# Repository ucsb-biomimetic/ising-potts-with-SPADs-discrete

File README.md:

# ising-potts-with-SPADs-discrete
CMOS compatible Ising and Potts Annealing Using Single-photon Avalanche Diodes: Design files

The proof-of-concept for SPAD Ising and Potts CTMC (continuous-time markov chain) relies on the key files provided here.  There are two sets of files for 16-circuit and 144-circuit implementations of variable rate SPADs; the 144-circuit version was created second, to enable demonstrations of combinatorial problem solving.

For each implementation, there are three groups of files: one for PCB design, one for FPGA logic, and one for data and code. The code runs tests on the physical system specified by the PCB and FPGA design, and saves data results.

For the 16-circuit version, both the code and the FPGA configuration for the system lies entirely on the Zedboard; a Vivado 2020.1 project is provided, which was used to create the Zedboard FPGA configuration. The processor side of the Zedboard was configured to run linux and the PYNQ environment, so data collection and control of the proof-of-concept aparatus was done through a jupyter-notebook running locally on the zedboard (and accessed from a PC over ethernet).

Since the provided jupyter notebook runs in concert with the Zedboard FPGA and the hardware we connect to the FPGA, it cannot be run in its entirety without fully replicating the hardware as well.  However, many intermediate data are saved alongside the notebook, so one may see the interaction between code and results.  

For the 144-circuit version, the FPGA logic was redesigned to expose a SPI interface that could be accessed over a USB connection. Thus the Python code ran directly on a PC.  In addition, the FPGA board (A Digilent Genesys 2) was configured using Vivado 2020.1 in non-project mode, so rather than a Vivado project, regular verilog files and a Vivado TCL script provided.

While many of the scripts still require a connection to the hardware to run correctly, some scripts that only perform data plotting can be run without the hardware.

All experimental data in the paper is drawn from one of the two experimental systems specified here.

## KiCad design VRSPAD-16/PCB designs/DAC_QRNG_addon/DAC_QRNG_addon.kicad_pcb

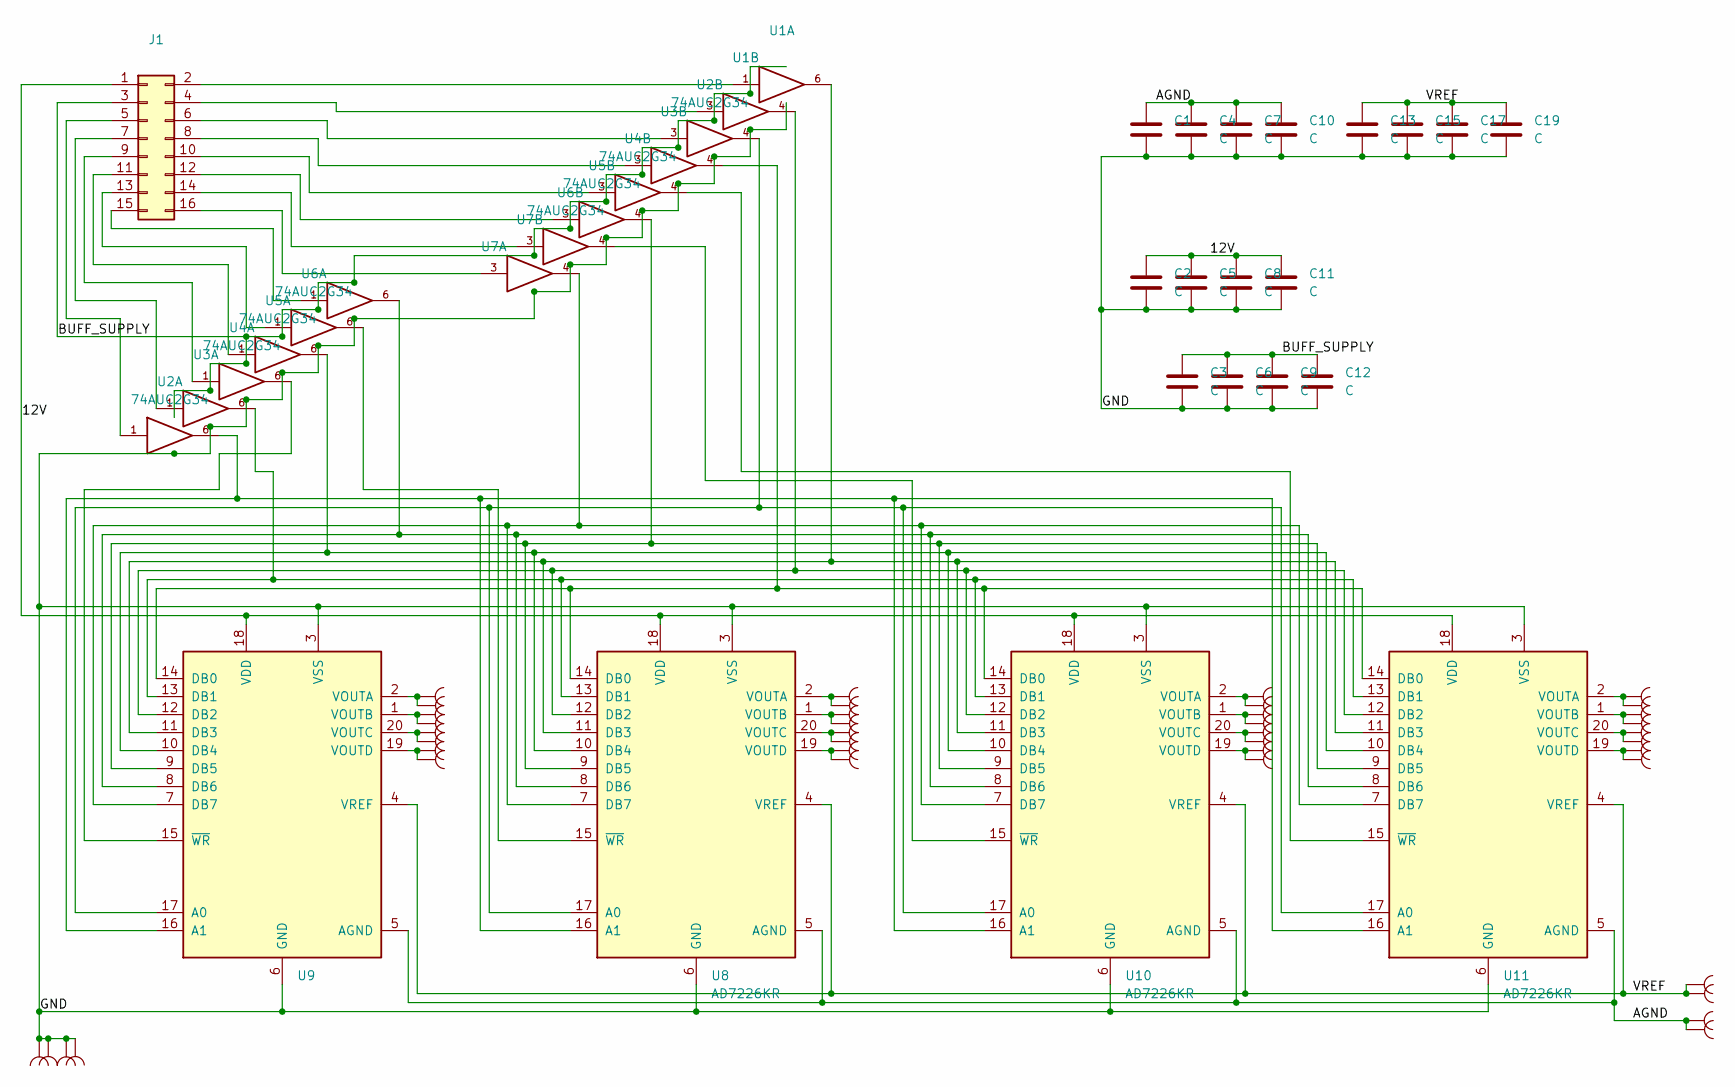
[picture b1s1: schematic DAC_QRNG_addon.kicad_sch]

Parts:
C1: (no value)
C2, C3, C4, C5, C6, C7, C8, C9, C10, C11, C12, C13, C15, C17, C19: C; C_0603_1608Metric_Pad1.08x0.95mm_HandSolder
J1: (no value)
U1, U3, U7, U9, U28, U29: (no value)
U2, U4, U5, U6: 74AUC2G34; SOT-363_SC-70-6
U8, U10, U11: AD7226KR; SOIC-20W_7.5x12.8mm_P1.27mm
U12, U13, U14, U15, U16, U17, U18, U19, U20, U21, U22, U23, U24, U25, U26, U27, U30, U31: Castle

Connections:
/12V: C2.1, C5.1, C8.1, C11.1, J1.1, U8.18 (VDD), U9.18 (VDD), U10.18 (VDD), U11.18 (VDD)
/AGND: C1.1, C4.1, C7.1, C10.1, U8.5 (AGND), U9.5 (AGND), U10.5 (AGND), U11.5 (AGND), U29.1, U29.2
/VREF: C13.1, C15.1, C17.1, C19.1, U8.4 (VREF), U9.4 (VREF), U10.4 (VREF), U11.4 (VREF), U28.1, U28.2
GND: C1.2, C2.2, C3.2, C4.2, C5.2, C6.2, C7.2, C8.2, C9.2, C10.2, C11.2, C12.2, C13.2, C15.2, C17.2, C19.2, U1.2 (GND), U2.2 (GND), U3.2 (GND), U4.2 (GND), U5.2 (GND), U6.2 (GND), U7.2 (GND), U8.3 (VSS), U8.6 (GND), U9.3 (VSS), U9.6 (GND), U10.3 (VSS), U10.6 (GND), U11.3 (VSS), U11.6 (GND), U30.1, U30.2, U31.1, U31.2
unnamed: J1.5, U2.1
unnamed: J1.6, U2.3
unnamed: J1.9, U4.1
unnamed: J1.10, U4.3
unnamed: J1.13, U6.1
unnamed: J1.14, U6.3
unnamed: J1.2, U1.1
unnamed: J1.4, U1.3
unnamed: J1.7, U3.1
unnamed: J1.8, U3.3
unnamed: J1.11, U5.1
unnamed: J1.12, U5.3
unnamed: U6.6, U8.15 (~WR)
unnamed: J1.15, U7.1
unnamed: J1.16, U7.3
unnamed: U4.6, U9.15 (~WR)
unnamed: U10.1 (VOUTB), U21.1, U21.2
unnamed: U10.2 (VOUTA), U20.1, U20.2
unnamed: U7.4, U8.7 (DB7), U9.7 (DB7), U10.7 (DB7), U11.7 (DB7)
unnamed: U7.6, U8.8 (DB6), U9.8 (DB6), U10.8 (DB6), U11.8 (DB6)
unnamed: U5.4, U8.9 (DB5), U9.9 (DB5), U10.9 (DB5), U11.9 (DB5)
unnamed: U5.6, U8.10 (DB4), U9.10 (DB4), U10.10 (DB4), U11.10 (DB4)
unnamed: U1.6, U8.11 (DB3), U9.11 (DB3), U10.11 (DB3), U11.11 (DB3)
unnamed: U1.4, U8.12 (DB2), U9.12 (DB2), U10.12 (DB2), U11.12 (DB2)
unnamed: U3.6, U8.13 (DB1), U9.13 (DB1), U10.13 (DB1), U11.13 (DB1)
unnamed: U3.4, U8.14 (DB0), U9.14 (DB0), U10.14 (DB0), U11.14 (DB0)
unnamed: U6.4, U10.15 (~WR)
unnamed: U2.6, U8.16 (A1), U9.16 (A1), U10.16 (A1), U11.16 (A1)
unnamed: U2.4, U8.17 (A0), U9.17 (A0), U10.17 (A0), U11.17 (A0)
unnamed: U10.19 (VOUTD), U23.1, U23.2
unnamed: U10.20 (VOUTC), U22.1, U22.2
unnamed: U11.1 (VOUTB), U25.1, U25.2
unnamed: U11.2 (VOUTA), U24.1, U24.2
unnamed: U4.4, U11.15 (~WR)
unnamed: U11.19 (VOUTD), U27.1, U27.2
unnamed: U11.20 (VOUTC), U26.1, U26.2
unnamed: U9.2 (VOUTA), U12.1, U12.2
unnamed: U9.1 (VOUTB), U13.1, U13.2
unnamed: U9.20 (VOUTC), U14.1, U14.2
unnamed: U9.19 (VOUTD), U15.1, U15.2
unnamed: U8.2 (VOUTA), U16.1, U16.2
unnamed: U8.1 (VOUTB), U17.1, U17.2
unnamed: U8.20 (VOUTC), U18.1, U18.2
unnamed: U8.19 (VOUTD), U19.1, U19.2
VCC: C3.1, C6.1, C9.1, C12.1, J1.3, U1.5 (VCC), U2.5 (VCC), U3.5 (VCC), U4.5 (VCC), U5.5 (VCC), U6.5 (VCC), U7.5 (VCC)

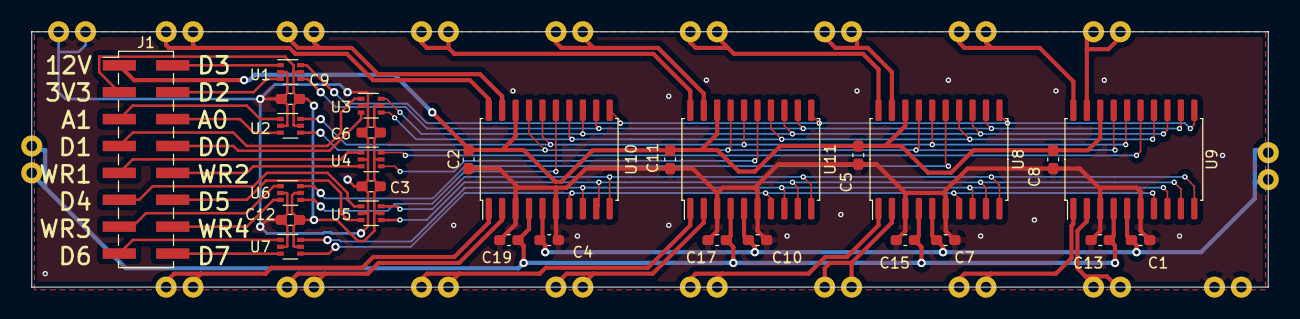
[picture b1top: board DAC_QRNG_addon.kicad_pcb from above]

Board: 2 copper layers, 116.8 x 24.1 mm, 48 parts (0 on the bottom side), 49 nets.

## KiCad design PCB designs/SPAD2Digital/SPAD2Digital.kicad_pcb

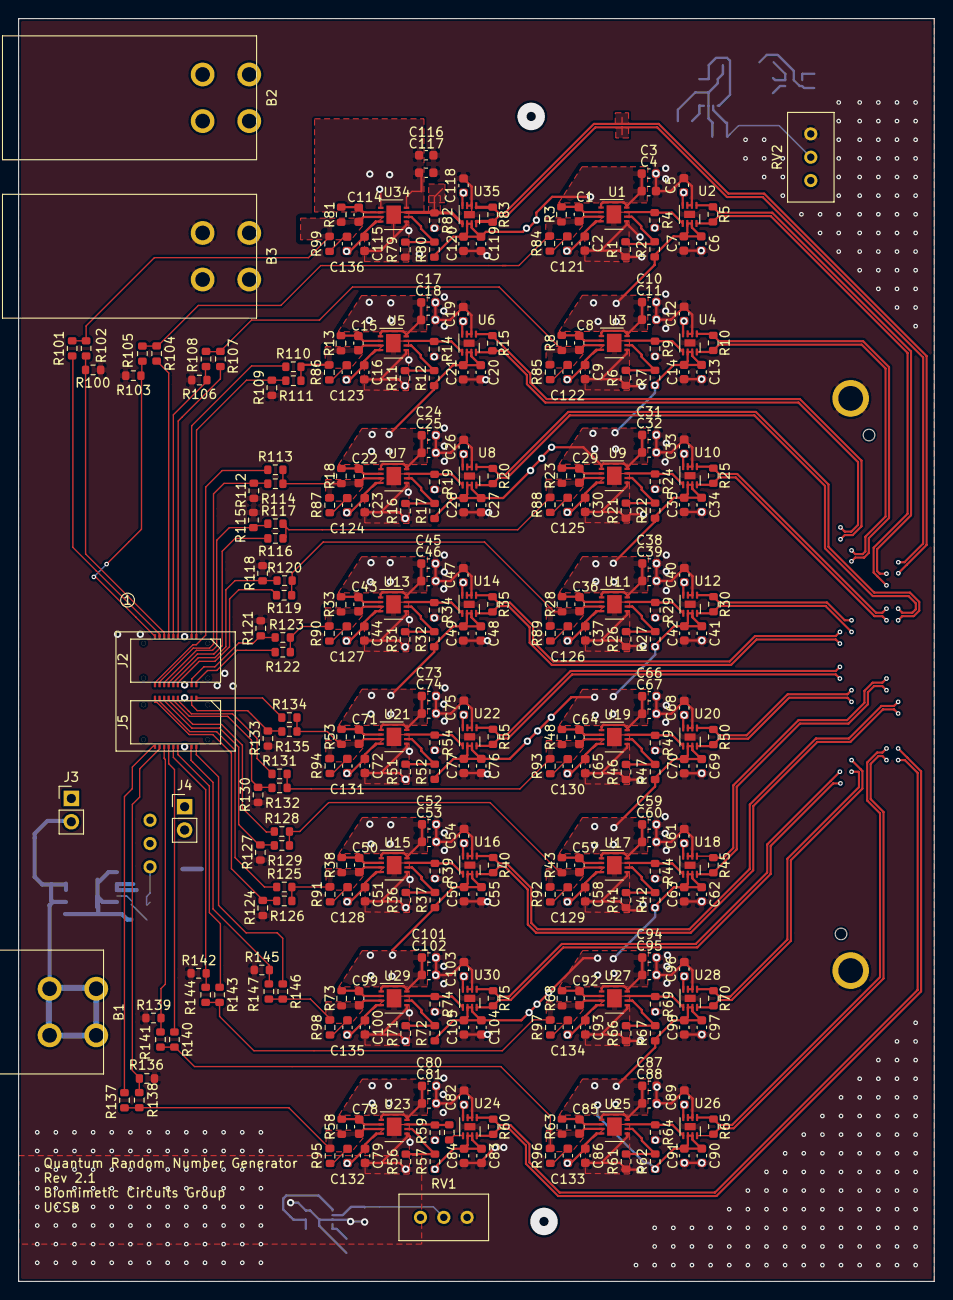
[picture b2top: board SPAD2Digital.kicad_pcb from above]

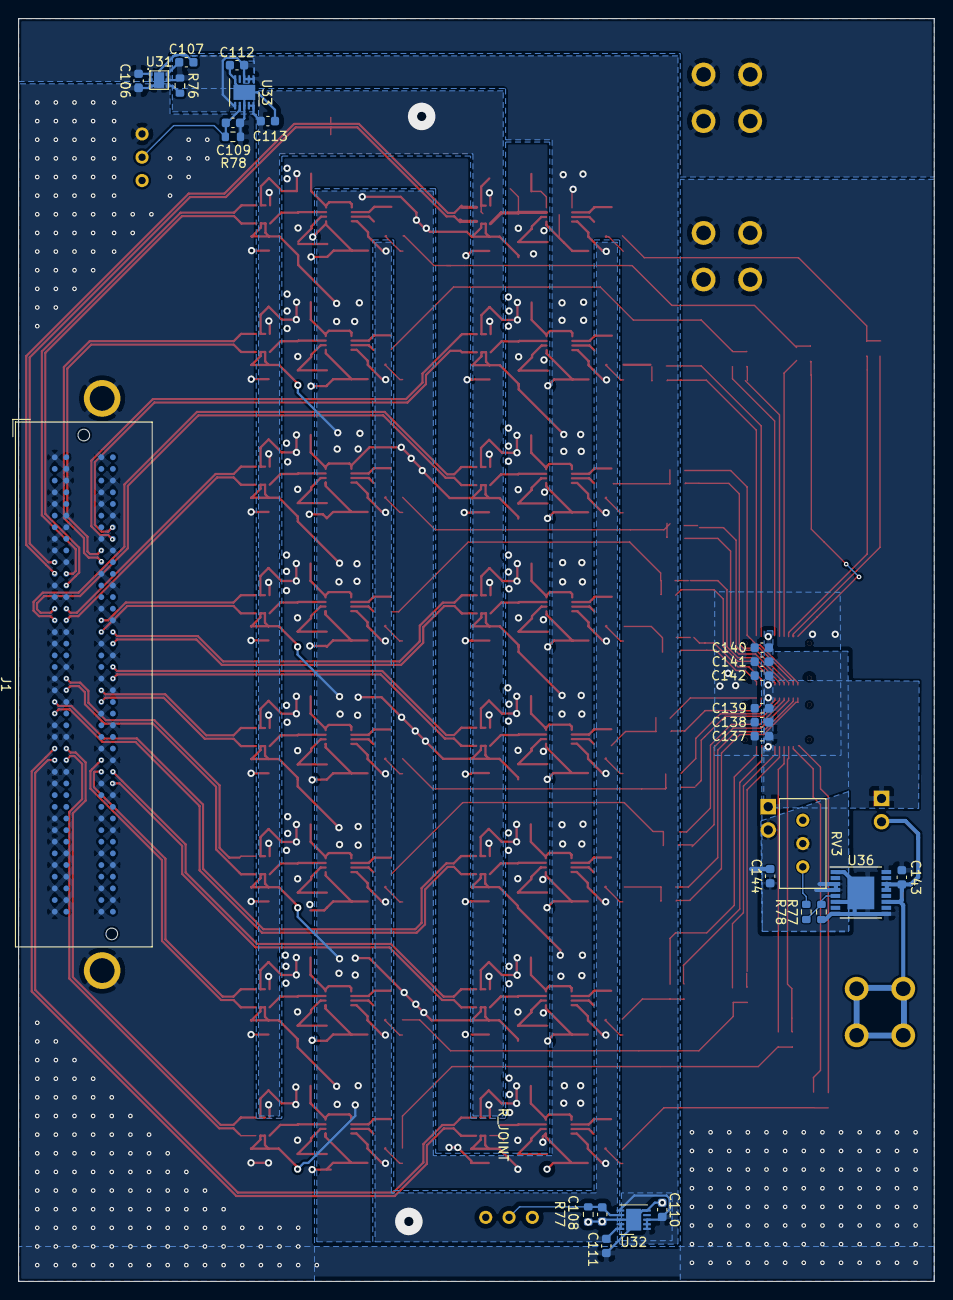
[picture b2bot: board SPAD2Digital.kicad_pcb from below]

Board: 4 copper layers, 99.8 x 137.7 mm, 341 parts (27 on the bottom side), 157 nets.

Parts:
B1, B2, B3: BANANA; CT3151-Horizontal
C1, C8, C15, C22, C29, C36, C43, C50, C57, C64, C71, C78, C85, C92, C99, C114: 100p; C_0603_1608Metric
C2, C3, C5, C6, C9, C10, C12, C13, C16, C17, C19, C20, C23, C24, C26, C27, C30, C31, C33, C34, C37, C38, C40, C41, C44, C45, C47, C48, C51, C52, C54, C55, C58, C59, C61, C62, C65, C66, C68, C69, C72, C73, C75, C76, C79, C80, C82, C83, C86, C87, C89, C90, C93, C94, C96, C97, C100, C101, C103, C104, C115, C116, C118, C119: 0.1u; C_0603_1608Metric
C4, C7, C11, C14, C18, C21, C25, C28, C32, C35, C39, C42, C46, C49, C53, C56, C60, C63, C67, C70, C74, C77, C81, C84, C88, C91, C95, C98, C102, C105, C117, C120, C137, C140: 1n; C_0603_1608Metric
C106, C138, C141, C143: 1u; C_0603_1608Metric
C107, C111, C113, C139, C142: 10u; C_0603_1608Metric
C108, C109, C110, C112: 4.7u; C_0603_1608Metric
C121, C122, C123, C124, C125, C126, C127, C128, C129, C130, C131, C132, C133, C134, C135, C136: 1p; C_0603_1608Metric
C144: 3.3u; C_0603_1608Metric
J1: Samtec_ASP-134603; Samtec_FMC_ASP-134604-01_4x40_Vertical
J2, J5: Hirose-DF17-20DS; Hirose_DF17-20DS_2x10_P0.50mm_Vertical_Mate
J3, J4: PinHeader_1x2; PinHeader_1x02_P2.54mm_Vertical
R1, R2, R6, R7, R11, R12, R16, R17, R21, R22, R26, R27, R31, R32, R36, R37, R41, R42, R46, R47, R51, R52, R56, R57, R61, R62, R66, R67, R71, R72, R79, R80, R100, R101, R102, R103, R104, R105, R106, R107, R108, R109, R110, R111, R112, R113, R114, R115, R116, R117, R118, R119, R120, R121, R122, R123, R124, R125, R126, R127, R128, R129, R130, R131, R132, R133, R134, R135, R136, R137, R138, R139, R140, R141, R142, R143, R144, R145, R146, R147: 0; R_0603_1608Metric
R3, R8, R13, R18, R23, R28, R33, R38, R43, R48, R53, R58, R63, R68, R73, R81: 240; R_0603_1608Metric
R4, R9, R14, R19, R24, R29, R34, R39, R44, R49, R54, R59, R64, R69, R74, R82: 500; R_0603_1608Metric
R5, R10, R15, R20, R25, R30, R35, R40, R45, R50, R55, R60, R65, R70, R75, R83: 100; R_0603_1608Metric
R76: 10K; R_0603_1608Metric
R77: 959; R_0603_1608Metric
R77#2: 2k; R_0603_1608Metric
R78: 15k; R_0603_1608Metric
R78#2: 1k; R_0603_1608Metric
R84, R85, R86, R87, R88, R89, R90, R91, R92, R93, R94, R95, R96, R97, R98, R99: 50; R_0603_1608Metric
RV1, RV2: 30k; Potentiometer_Bourns_3296W_Vertical
RV3: 15k; Potentiometer_Bourns_3296W_Vertical
R_JOINT: 0; R_0603_1608Metric
U1, U3, U5, U7, U9, U11, U13, U15, U17, U19, U21, U23, U25, U27, U29, U34: LMH6629-NGQ08A; WSON-8-1EP_3x3mm_P0.5mm_EP1.6x2.0mm
U2, U4, U6, U8, U10, U12, U14, U16, U18, U20, U22, U24, U26, U28, U30, U35: MAX40026; TDFN-8-1EP_2x2mm_P0.5mm_EP0.8x1.2mm
U31: NCP187; WDFN-6-1EP_2x2mm_P0.65mm_EP1.12x1.72
U32, U33: LTC3045; DFN-10-1EP_3x3mm_P0.5mm_EP1.65x2.38mm
U36: LT3012; TSSOP-16-1EP_4.4x5mm_P0.65mm

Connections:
3.3V: C3.1, C4.1, C6.1, C7.1, C10.1, C11.1, C13.1, C14.1, C17.1, C18.1, C20.1, C21.1, C24.1, C25.1, C27.1, C28.1, C31.1, C32.1, C34.1, C35.1, C38.1, C39.1, C41.1, C42.1, C45.1, C46.1, C48.1, C49.1, C52.1, C53.1, C55.1, C56.1, C59.1, C60.1, C62.1, C63.1, C66.1, C67.1, C69.1, C70.1, C73.1, C74.1, C76.1, C77.1, C80.1, C81.1, C83.1, C84.1, C87.1, C88.1, C90.1, C91.1, C94.1, C95.1, C97.1, C98.1, C101.1, C102.1, C104.1, C105.1, C107.1, C110.1, C112.1, C116.1, C117.1, C119.1, C120.1, R2.1, R7.1, R12.1, R17.1, R22.1, R27.1, R32.1, R37.1, R42.1, R47.1, R52.1, R57.1, R62.1, R67.1, R72.1, R76.1, R80.1, U1.1, U1.8, U2.6, U2.7, U3.1, U3.8, U4.6, U4.7, U5.1, U5.8, U6.6, U6.7, U7.1, U7.8, U8.6, U8.7, U9.1, U9.8, U10.6, U10.7, U11.1, U11.8, U12.6, U12.7, U13.1, U13.8, U14.6, U14.7, U15.1, U15.8, U16.6, U16.7, U17.1, U17.8, U18.6, U18.7, U19.1, U19.8, U20.6, U20.7, U21.1, U21.8, U22.6, U22.7, U23.1, U23.8, U24.6, U24.7, U25.1, U25.8, U26.6, U26.7, U27.1, U27.8, U28.6, U28.7, U29.1, U29.8, U30.6, U30.7, U31.5, U31.6, U32.1, U32.2, U32.3, U32.6, U33.1, U33.2, U33.3, U33.6, U34.1, U34.8, U35.6, U35.7
/A1: C114.2, R81.2, R99.2, R101.2, R102.2, U34.3
/A1_OUT_N: J1.C11, R83.2, U35.1
/A1_OUT_P: J1.C10, R83.1, U35.8
/A2: C1.2, R3.2, R84.2, R104.2, R105.2, U1.3
/A2_OUT_N: J1.D11, R5.2, U2.1
/A2_OUT_P: J1.D12, R5.1, U2.8
/A3: C8.2, R8.2, R85.2, R107.2, R108.2, U3.3
/A3_OUT_N: J1.G10, R10.2, U4.1
/A3_OUT_P: J1.G09, R10.1, U4.8
/A4: C15.2, R13.2, R86.2, R110.2, R111.2, U5.3
/A4_OUT_N: J1.H08, R15.2, U6.1
/A4_OUT_P: J1.H07, R15.1, U6.8
/B1: C22.2, R18.2, R87.2, R113.2, R114.2, U7.3
/B1_OUT_N: J1.C15, R20.2, U8.1
/B1_OUT_P: J1.C14, R20.1, U8.8
/B2: C29.2, R23.2, R88.2, R116.2, R117.2, U9.3
/B2_OUT_N: J1.D14, R25.2, U10.1
/B2_OUT_P: J1.D15, R25.1, U10.8
/B3: C36.2, R28.2, R89.2, R119.2, R120.2, U11.3
/B3_OUT_N: J1.G15, R30.2, U12.1
/B3_OUT_P: J1.G16, R30.1, U12.8
/B4: C43.2, R33.2, R90.2, R122.2, R123.2, U13.3
/B4_OUT_N: J1.H16, R35.2, U14.1
/B4_OUT_P: J1.H17, R35.1, U14.8
/C1: C50.2, R38.2, R91.2, R125.2, R126.2, U15.3
/C1_OUT_N: J1.C22, R40.2, U16.1
/C1_OUT_P: J1.C23, R40.1, U16.8
/C2: C57.2, R43.2, R92.2, R128.2, R129.2, U17.3
/C2_OUT_N: J1.D20, R45.2, U18.1
/C2_OUT_P: J1.D21, R45.1, U18.8
/C3: C64.2, R48.2, R93.2, R131.2, R132.2, U19.3
/C3_OUT_N: J1.G21, R50.2, U20.1
/C3_OUT_P: J1.G22, R50.1, U20.8
/C4: C71.2, R53.2, R94.2, R134.2, R135.2, U21.3
/C4_OUT_N: J1.H19, R55.2, U22.1
/C4_OUT_P: J1.H20, R55.1, U22.8
/Channel_A1/TIA_FB: C114.1, R81.1, U34.2
/Channel_A1/TIA_OUT: R82.1, U34.7, U35.5
/Channel_A2/TIA_FB: C1.1, R3.1, U1.2
/Channel_A2/TIA_OUT: R4.1, U1.7, U2.5
/Channel_A3/TIA_FB: C8.1, R8.1, U3.2
/Channel_A3/TIA_OUT: R9.1, U3.7, U4.5
/Channel_A4/TIA_FB: C15.1, R13.1, U5.2
/Channel_A4/TIA_OUT: R14.1, U5.7, U6.5
/Channel_B1/TIA_FB: C22.1, R18.1, U7.2
/Channel_B1/TIA_OUT: R19.1, U7.7, U8.5
/Channel_B2/TIA_FB: C29.1, R23.1, U9.2
/Channel_B2/TIA_OUT: R24.1, U9.7, U10.5
/Channel_B3/TIA_FB: C36.1, R28.1, U11.2
/Channel_B3/TIA_OUT: R29.1, U11.7, U12.5
/Channel_B4/TIA_FB: C43.1, R33.1, U13.2
/Channel_B4/TIA_OUT: R34.1, U13.7, U14.5
/Channel_C1/TIA_FB: C50.1, R38.1, U15.2
/Channel_C1/TIA_OUT: R39.1, U15.7, U16.5
/Channel_C2/TIA_FB: C57.1, R43.1, U17.2
/Channel_C2/TIA_OUT: R44.1, U17.7, U18.5
/Channel_C3/TIA_FB: C64.1, R48.1, U19.2
/Channel_C3/TIA_OUT: R49.1, U19.7, U20.5
/Channel_C4/TIA_FB: C71.1, R53.1, U21.2
/Channel_C4/TIA_OUT: R54.1, U21.7, U22.5
/Channel_D1/TIA_FB: C78.1, R58.1, U23.2
/Channel_D1/TIA_OUT: R59.1, R_JOINT.1, R_JOINT.2, U23.7, U24.5
/Channel_D2/TIA_FB: C85.1, R63.1, U25.2
/Channel_D2/TIA_OUT: R64.1, U25.7, U26.5
/Channel_D3/TIA_FB: C92.1, R68.1, U27.2
/Channel_D3/TIA_OUT: R69.1, U27.7, U28.5
/Channel_D4/TIA_FB: C99.1, R73.1, U29.2
/Channel_D4/TIA_OUT: R74.1, U29.7, U30.5
/D1: C78.2, R58.2, R95.2, R137.2, R138.2, U23.3
/D1_OUT_N: J1.C27, R60.2, U24.1
/D1_OUT_P: J1.C26, R60.1, U24.8
/D2: C85.2, R63.2, R96.2, R140.2, R141.2, U25.3
/D2_OUT_N: J1.D26, R65.2, U26.1
/D2_OUT_P: J1.D27, R65.1, U26.8
/D3: C92.2, R68.2, R97.2, R143.2, R144.2, U27.3
/D3_OUT_N: J1.G28, R70.2, U28.1
/D3_OUT_P: J1.G27, R70.1, U28.8
/D4: C99.2, R73.2, R98.2, R146.2, R147.2, U29.3
/D4_OUT_N: J1.H28, R75.2, U30.1
/D4_OUT_P: J1.H29, R75.1, U30.8
/SPAD Sheet/Fast1: J2.2, R101.1
/SPAD Sheet/Fast2: J2.4, R104.1
/SPAD Sheet/Fast3: J2.6, R107.1
/SPAD Sheet/Fast4: J2.9, R110.1
/SPAD Sheet/Fast5: J2.20, R113.1
/SPAD Sheet/Fast6: J2.17, R116.1
/SPAD Sheet/Fast7: J2.15, R119.1
/SPAD Sheet/Fast8: J2.11, R122.1
/SPAD Sheet/Fast9: J5.2, R125.1
/SPAD Sheet/Fast10: J5.4, R128.1
/SPAD Sheet/Fast11: J5.6, R131.1
/SPAD Sheet/Fast12: J5.10, R134.1
/SPAD Sheet/Fast13: J5.20, R137.1
/SPAD Sheet/Fast14: J5.17, R140.1
/SPAD Sheet/Fast15: J5.15, R143.1
/SPAD Sheet/Fast16: J5.11, R146.1
/SPAD Sheet/Slow1: J2.3, R100.1, R102.1
/SPAD Sheet/Slow2: J2.1, R103.1, R105.1
/SPAD Sheet/Slow3: J2.5, R106.1, R108.1
/SPAD Sheet/Slow4: J2.10, R109.1, R111.1
/SPAD Sheet/Slow5: J2.19, R112.1, R114.1
/SPAD Sheet/Slow6: J2.18, R115.1, R117.1
/SPAD Sheet/Slow7: J2.16, R118.1, R120.1
/SPAD Sheet/Slow8: J2.12, R121.1, R123.1
/SPAD Sheet/Slow9: J5.1, R124.1, R126.1
/SPAD Sheet/Slow10: J5.3, R127.1, R129.1
/SPAD Sheet/Slow11: J5.5, R130.1, R132.1
/SPAD Sheet/Slow12: J5.9, R133.1, R135.1
/SPAD Sheet/Slow13: J5.19, R136.1, R138.1
/SPAD Sheet/Slow14: J5.18, R139.1, R141.1
/SPAD Sheet/Slow15: J5.16, R142.1, R144.1
/SPAD Sheet/Slow16: J5.12, R145.1, R147.1
COMP_REF: C5.1, C12.1, C19.1, C26.1, C33.1, C40.1, C47.1, C54.1, C61.1, C68.1, C75.1, C82.1, C89.1, C96.1, C103.1, C113.1, C118.1, U2.4, U4.4, U6.4, U8.4, U10.4, U12.4, U14.4, U16.4, U18.4, U20.4, U22.4, U24.4, U26.4, U28.4, U30.4, U33.9, U33.10, U35.4
GND: B3.1, C2.2, C3.2, C4.2, C5.2, C6.2, C7.2, C9.2, C10.2, C11.2, C12.2, C13.2, C14.2, C16.2, C17.2, C18.2, C19.2, C20.2, C21.2, C23.2, C24.2, C25.2, C26.2, C27.2, C28.2, C30.2, C31.2, C32.2, C33.2, C34.2, C35.2, C37.2, C38.2, C39.2, C40.2, C41.2, C42.2, C44.2, C45.2, C46.2, C47.2, C48.2, C49.2, C51.2, C52.2, C53.2, C54.2, C55.2, C56.2, C58.2, C59.2, C60.2, C61.2, C62.2, C63.2, C65.2, C66.2, C67.2, C68.2, C69.2, C70.2, C72.2, C73.2, C74.2, C75.2, C76.2, C77.2, C79.2, C80.2, C81.2, C82.2, C83.2, C84.2, C86.2, C87.2, C88.2, C89.2, C90.2, C91.2, C93.2, C94.2, C95.2, C96.2, C97.2, C98.2, C100.2, C101.2, C102.2, C103.2, C104.2, C105.2, C106.2, C107.2, C108.2, C109.2, C110.2, C111.2, C112.2, C113.2, C115.2, C116.2, C117.2, C118.2, C119.2, C120.2, C137.2, C138.2, C139.2, C140.2, C141.2, C142.2, C143.2, C144.1, J1.C01, J1.C04, J1.C05, J1.C08, J1.C09, J1.C12, J1.C13, J1.C16, J1.C17, J1.C20, J1.C21, J1.C24, J1.C25, J1.C28, J1.C29, J1.C32, J1.C33, J1.C34, J1.C36, J1.C38, J1.C40, J1.D02, J1.D03, J1.D06, J1.D07, J1.D10, J1.D13, J1.D16, J1.D19, J1.D22, J1.D25, J1.D28, J1.D35, J1.D37, J1.D39, J1.G01, J1.G04, J1.G05, J1.G08, J1.G11, J1.G14, J1.G17, J1.G20, J1.G23, J1.G26, J1.G29, J1.G32, J1.G35, J1.G38, J1.G40, J1.H03, J1.H06, J1.H09, J1.H12, J1.H15, J1.H18, J1.H21, J1.H24, J1.H27, J1.H30, J1.H33, J1.H36, J1.H39, R1.1, R4.2, R6.1, R9.2, R11.1, R14.2, R16.1, R19.2, R21.1, R24.2, R26.1, R29.2, R31.1, R34.2, R36.1, R39.2, R41.1, R44.2, R46.1, R49.2, R51.1, R54.2, R56.1, R59.2, R61.1, R64.2, R66.1, R69.2, R71.1, R74.2, R77.2, R77#2.2, R78#2.2, R79.1, R82.2, R100.2, R103.2, R106.2, R109.2, R112.2, R115.2, R118.2, R121.2, R124.2, R127.2, R130.2, R133.2, R136.2, R139.2, R142.2, R145.2, RV1.1, RV2.1, U1.5, U1.9, U2.2, U2.3, U2.9, U3.5, U3.9, U4.2, U4.3, U4.9, U5.5, U5.9, U6.2, U6.3, U6.9, U7.5, U7.9, U8.2, U8.3, U8.9, U9.5, U9.9, U10.2, U10.3, U10.9, U11.5, U11.9, U12.2, U12.3, U12.9, U13.5, U13.9, U14.2, U14.3, U14.9, U15.5, U15.9, U16.2, U16.3, U16.9, U17.5, U17.9, U18.2, U18.3, U18.9, U19.5, U19.9, U20.2, U20.3, U20.9, U21.5, U21.9, U22.2, U22.3, U22.9, U23.5, U23.9, U24.2, U24.3, U24.9, U25.5, U25.9, U26.2, U26.3, U26.9, U27.5, U27.9, U28.2, U28.3, U28.9, U29.5, U29.9, U30.2, U30.3, U30.9, U31.3, U31.7, U32.5, U32.8, U32.11, U33.5, U33.8, U33.11, U34.5, U34.9, U35.2, U35.3, U35.9, U36.1, U36.6, U36.8, U36.9, U36.16, U36.17
HV: C137.1, C138.1, C139.1, C140.1, C141.1, C142.1, J2.7, J2.8, J2.13, J2.14, J3.1, J4.1, J5.7, J5.8, J5.13, J5.14
IN_HV: B1.1, C143.1, J3.2, U36.11, U36.13, U36.14
IN_PWR: B2.1, C106.1, U31.1, U31.2
unnamed: C108.1, R77#2.1, RV1.2, U32.7
unnamed: C109.1, R78#2.1, RV2.2, U33.7
unnamed: C121.2, R84.1
unnamed: C122.2, R85.1
unnamed: C123.2, R86.1
unnamed: C124.2, R87.1
unnamed: C125.2, R88.1
unnamed: C126.2, R89.1
unnamed: C127.2, R90.1
unnamed: C128.2, R91.1
unnamed: C129.2, R92.1
unnamed: C130.2, R93.1
unnamed: C131.2, R94.1
unnamed: C132.2, R95.1
unnamed: C133.2, R96.1
unnamed: C134.2, R97.1
unnamed: C135.2, R98.1
unnamed: C136.2, R99.1
unnamed: C144.2, J4.2, RV3.2, U36.3, U36.4
unnamed: R1.2, R2.2, U1.6
unnamed: R6.2, R7.2, U3.6
unnamed: R11.2, R12.2, U5.6
unnamed: R16.2, R17.2, U7.6
unnamed: R21.2, R22.2, U9.6
unnamed: R26.2, R27.2, U11.6
unnamed: R31.2, R32.2, U13.6
unnamed: R36.2, R37.2, U15.6
unnamed: R41.2, R42.2, U17.6
unnamed: R46.2, R47.2, U19.6
unnamed: R51.2, R52.2, U21.6
unnamed: R56.2, R57.2, U23.6
unnamed: R61.2, R62.2, U25.6
unnamed: R66.2, R67.2, U27.6
unnamed: R71.2, R72.2, U29.6
unnamed: R76.2, U31.4
unnamed: R77.1, R78.2, U36.5
unnamed: R78.1, RV3.1
unnamed: R79.2, R80.2, U34.6
TIA_REF: C2.1, C9.1, C16.1, C23.1, C30.1, C37.1, C44.1, C51.1, C58.1, C65.1, C72.1, C79.1, C86.1, C93.1, C100.1, C111.1, C115.1, C121.1, C122.1, C123.1, C124.1, C125.1, C126.1, C127.1, C128.1, C129.1, C130.1, C131.1, C132.1, C133.1, C134.1, C135.1, C136.1, U1.4, U3.4, U5.4, U7.4, U9.4, U11.4, U13.4, U15.4, U17.4, U19.4, U21.4, U23.4, U25.4, U27.4, U29.4, U32.9, U32.10, U34.4

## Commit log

2023-01-04 Add files via upload
    Added PCB designs, operating code and Jupyter notebook from Zedboard local space, and a Vivado 2020.1 project for Zedboard configuration.
2023-06-14 added design files for 144-circuit experimental demonstration
2023-06-14 updated readme to reflect 144-circuit system
